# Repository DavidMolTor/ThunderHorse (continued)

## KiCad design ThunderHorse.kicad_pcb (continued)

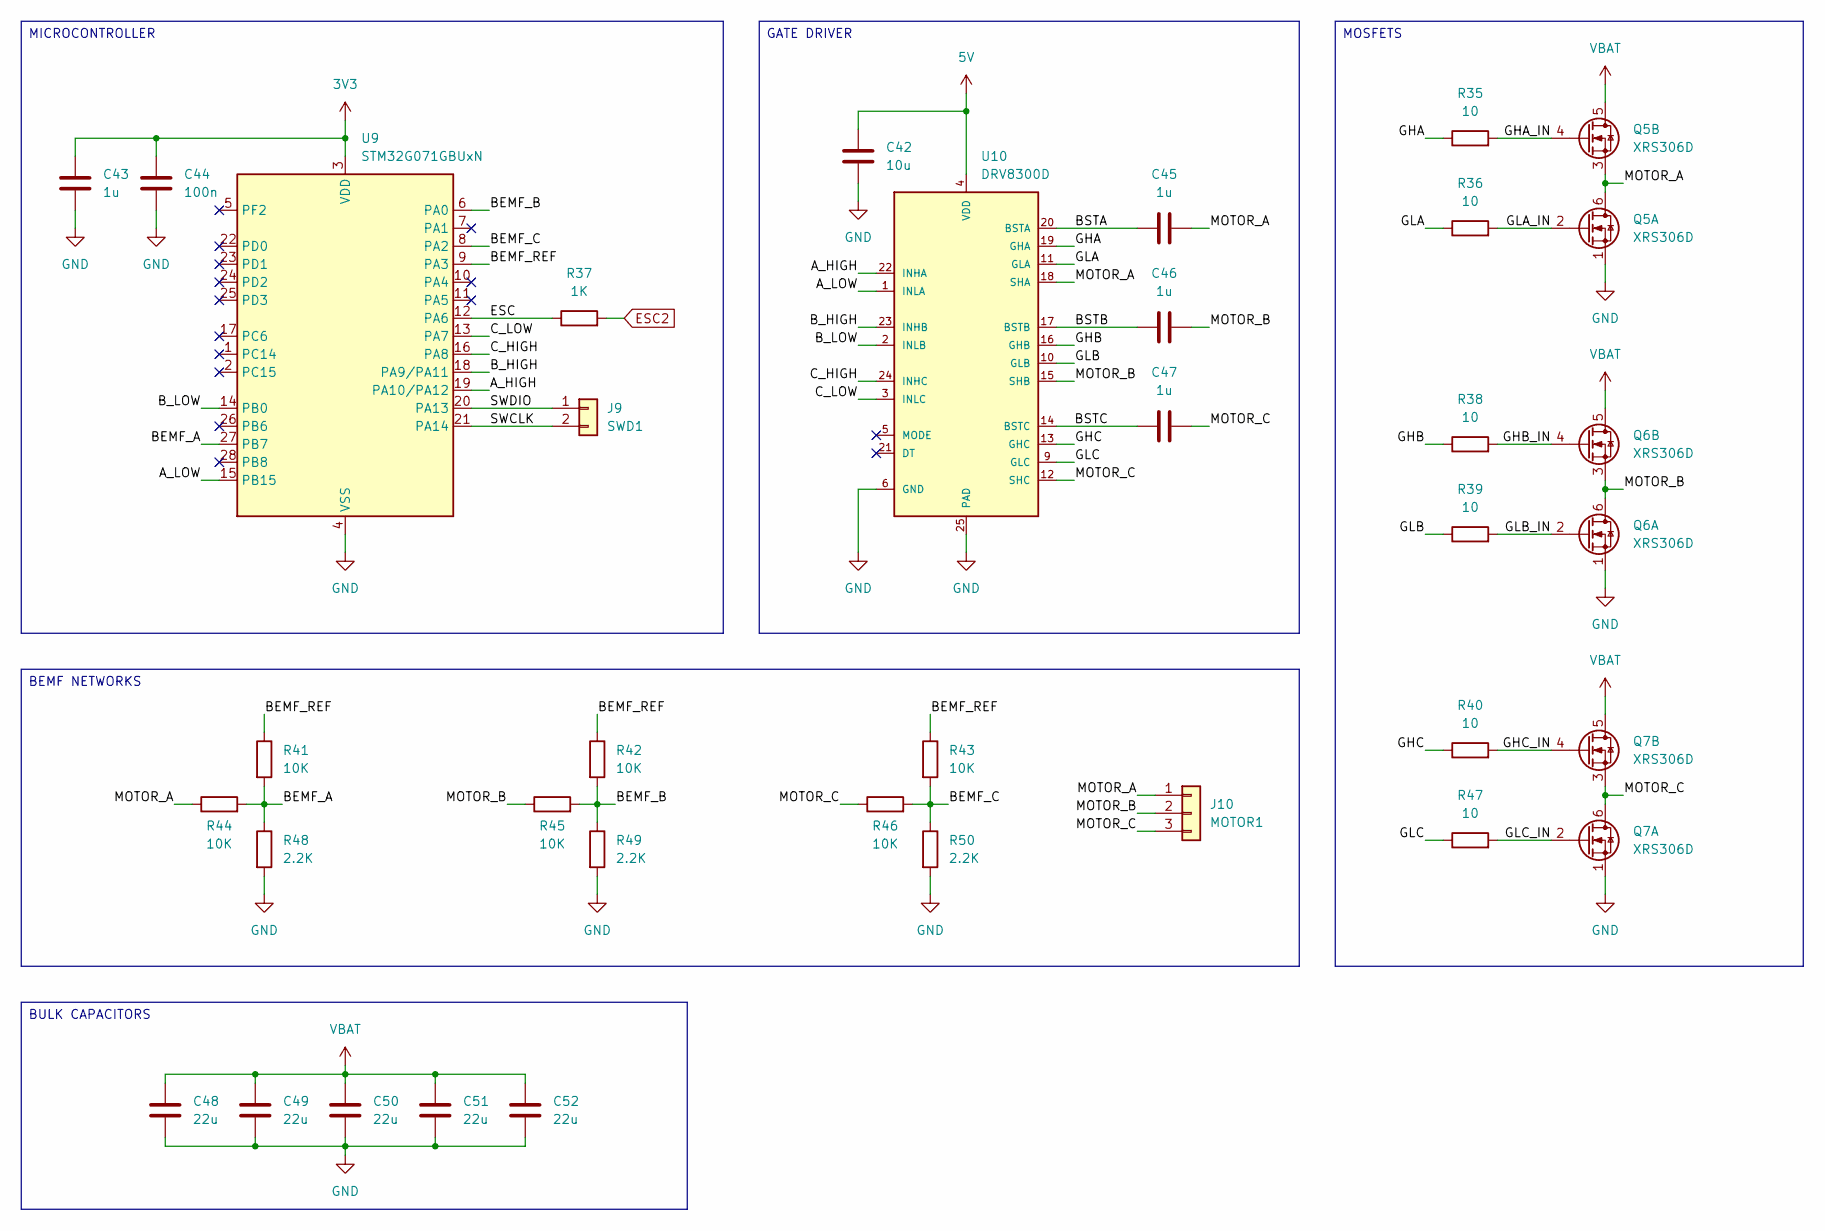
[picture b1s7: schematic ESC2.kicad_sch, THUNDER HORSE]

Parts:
C42: 10u; C_0603_1608Metric
C43, C45, C46, C47: 1u; C_0603_1608Metric
C44: 100n; C_0603_1608Metric
C48, C49, C50, C51, C52: 22u; C_1206_3216Metric
J9: SWD1; PAD_2_SQUARE_SOLID_1.0x1.0mm_P1.5mm
J10: MOTOR1; PAD_3_SQUARE_SOLID_2.5x2.5mm_P4.0mm_MOTOR
Q5, Q6, Q7: XRS306D; PDFN8_DUAL_3.3x3.3mm
R35, R36, R38, R39, R40, R47: 10; R_0603_1608Metric
R37: 1K; R_0603_1608Metric
R41, R42, R43, R44, R45, R46: 10K; R_0603_1608Metric
R48, R49, R50: 2.2K; R_0603_1608Metric
U9: STM32G071GBUxN; QFN-28_4x4mm_P0.5mm
U10: DRV8300D; VQFN-24-1EP_4x4mm_P0.5mm_EP2.45x2.45mm

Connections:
3V3: C43.1, C44.1, U9.3 (VDD); also elsewhere on the board
5V: C42.1, U10.4 (VDD); also elsewhere on the board
/ESC/ESC2/A_HIGH: U9.19 (PA10/PA12), U10.22 (INHA)
/ESC/ESC2/A_LOW: U9.15 (PB15), U10.1 (INLA)
/ESC/ESC2/BEMF_A: R41.2, R44.2, R48.1, U9.27 (PB7)
/ESC/ESC2/BEMF_B: R42.2, R45.2, R49.1, U9.6 (PA0)
/ESC/ESC2/BEMF_C: R43.2, R46.2, R50.1, U9.8 (PA2)
/ESC/ESC2/BEMF_REF: R41.1, R42.1, R43.1, U9.9 (PA3)
/ESC/ESC2/BSTA: C45.1, U10.20 (BSTA)
/ESC/ESC2/BSTB: C46.1, U10.17 (BSTB)
/ESC/ESC2/BSTC: C47.1, U10.14 (BSTC)
/ESC/ESC2/B_HIGH: U9.18 (PA9/PA11), U10.23 (INHB)
/ESC/ESC2/B_LOW: U9.14 (PB0), U10.2 (INLB)
/ESC/ESC2/C_HIGH: U9.16 (PA8), U10.24 (INHC)
/ESC/ESC2/C_LOW: U9.13 (PA7), U10.3 (INLC)
/ESC/ESC2/ESC: R37.1, U9.12 (PA6)
/ESC/ESC2/GHA: R35.1, U10.19 (GHA)
/ESC/ESC2/GHA_IN: Q5.4 (G), R35.2
/ESC/ESC2/GHB: R38.1, U10.16 (GHB)
/ESC/ESC2/GHB_IN: Q6.4 (G), R38.2
/ESC/ESC2/GHC: R40.1, U10.13 (GHC)
/ESC/ESC2/GHC_IN: Q7.4 (G), R40.2
/ESC/ESC2/GLA: R36.1, U10.11 (GLA)
/ESC/ESC2/GLA_IN: Q5.2 (G), R36.2
/ESC/ESC2/GLB: R39.1, U10.10 (GLB)
/ESC/ESC2/GLB_IN: Q6.2 (G), R39.2
/ESC/ESC2/GLC: R47.1, U10.9 (GLC)
/ESC/ESC2/GLC_IN: Q7.2 (G), R47.2
/ESC/ESC2/MOTOR_A: C45.2, J10.1, Q5.3 (S), Q5.6 (D), R44.1, U10.18 (SHA)
/ESC/ESC2/MOTOR_B: C46.2, J10.2, Q6.3 (S), Q6.6 (D), R45.1, U10.15 (SHB)
/ESC/ESC2/MOTOR_C: C47.2, J10.3, Q7.3 (S), Q7.6 (D), R46.1, U10.12 (SHC)
/ESC/ESC2/SWCLK: J9.2, U9.21 (PA14)
/ESC/ESC2/SWDIO: J9.1, U9.20 (PA13)
ESC2: R37.2; also elsewhere on the board
GND: C42.2, C43.2, C44.2, C48.2, C49.2, C50.2, C51.2, C52.2, Q5.1 (S), Q6.1 (S), Q7.1 (S), R48.2, R49.2, R50.2, U9.4 (VSS), U10.6 (GND), U10.25 (PAD); also elsewhere on the board
VBAT: C48.1, C49.1, C50.1, C51.1, C52.1, Q5.5 (D), Q6.5 (D), Q7.5 (D); also elsewhere on the board

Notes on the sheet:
MICROCONTROLLER
BULK CAPACITORS
BEMF NETWORKS
MOSFETS
GATE DRIVER

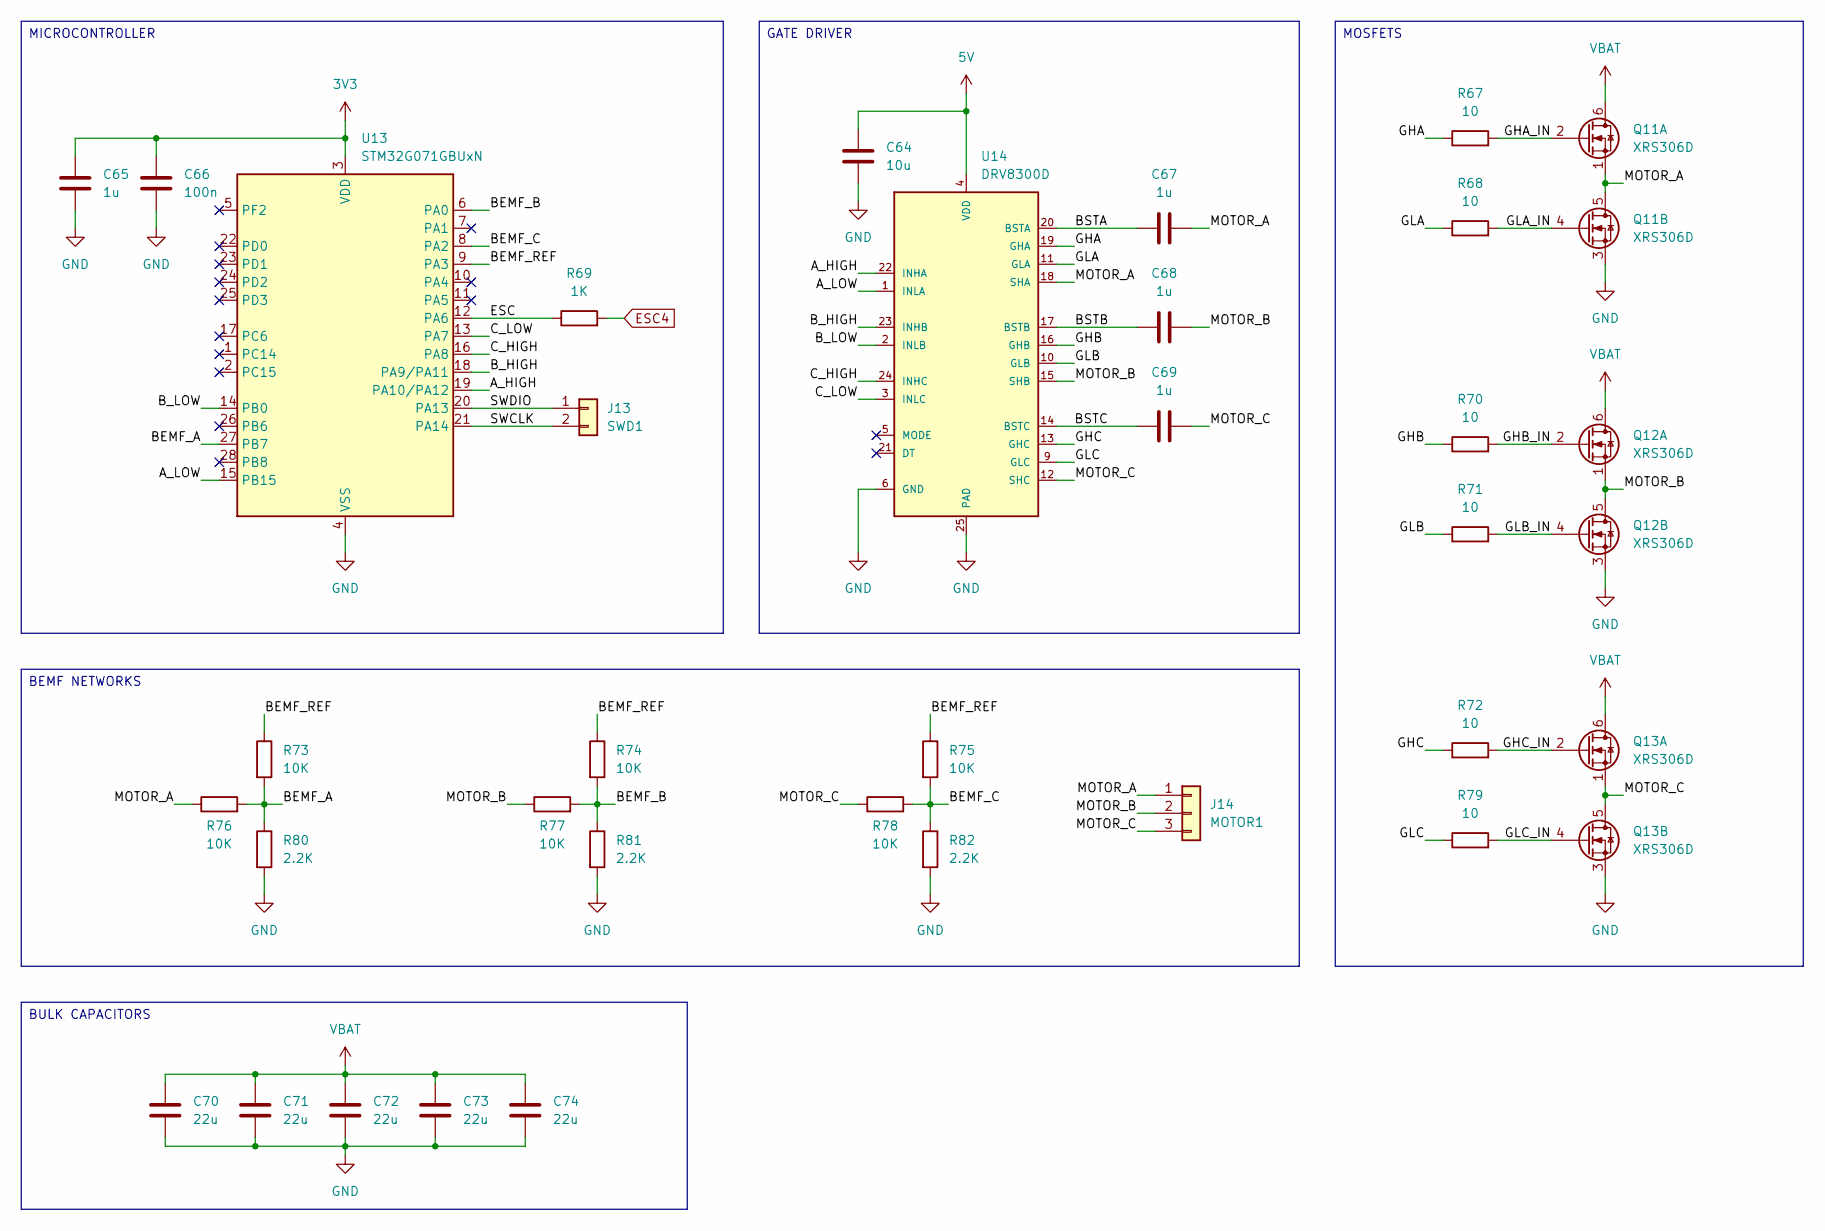
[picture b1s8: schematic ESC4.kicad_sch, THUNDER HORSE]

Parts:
C64: 10u; C_0603_1608Metric
C65, C67, C68, C69: 1u; C_0603_1608Metric
C66: 100n; C_0603_1608Metric
C70, C71, C72, C73, C74: 22u; C_1206_3216Metric
J13: SWD1; PAD_2_SQUARE_SOLID_1.0x1.0mm_P1.5mm
J14: MOTOR1; PAD_3_SQUARE_SOLID_2.5x2.5mm_P4.0mm_MOTOR
Q11, Q12, Q13: XRS306D; PDFN8_DUAL_3.3x3.3mm
R67, R68, R70, R71, R72, R79: 10; R_0603_1608Metric
R69: 1K; R_0603_1608Metric
R73, R74, R75, R76, R77, R78: 10K; R_0603_1608Metric
R80, R81, R82: 2.2K; R_0603_1608Metric
U13: STM32G071GBUxN; QFN-28_4x4mm_P0.5mm
U14: DRV8300D; VQFN-24-1EP_4x4mm_P0.5mm_EP2.45x2.45mm

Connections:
3V3: C65.1, C66.1, U13.3 (VDD); also elsewhere on the board
5V: C64.1, U14.4 (VDD); also elsewhere on the board
/ESC/ESC4/A_HIGH: U13.19 (PA10/PA12), U14.22 (INHA)
/ESC/ESC4/A_LOW: U13.15 (PB15), U14.1 (INLA)
/ESC/ESC4/BEMF_A: R73.2, R76.2, R80.1, U13.27 (PB7)
/ESC/ESC4/BEMF_B: R74.2, R77.2, R81.1, U13.6 (PA0)
/ESC/ESC4/BEMF_C: R75.2, R78.2, R82.1, U13.8 (PA2)
/ESC/ESC4/BEMF_REF: R73.1, R74.1, R75.1, U13.9 (PA3)
/ESC/ESC4/BSTA: C67.1, U14.20 (BSTA)
/ESC/ESC4/BSTB: C68.1, U14.17 (BSTB)
/ESC/ESC4/BSTC: C69.1, U14.14 (BSTC)
/ESC/ESC4/B_HIGH: U13.18 (PA9/PA11), U14.23 (INHB)
/ESC/ESC4/B_LOW: U13.14 (PB0), U14.2 (INLB)
/ESC/ESC4/C_HIGH: U13.16 (PA8), U14.24 (INHC)
/ESC/ESC4/C_LOW: U13.13 (PA7), U14.3 (INLC)
/ESC/ESC4/ESC: R69.1, U13.12 (PA6)
/ESC/ESC4/GHA: R67.1, U14.19 (GHA)
/ESC/ESC4/GHA_IN: Q11.2 (G), R67.2
/ESC/ESC4/GHB: R70.1, U14.16 (GHB)
/ESC/ESC4/GHB_IN: Q12.2 (G), R70.2
/ESC/ESC4/GHC: R72.1, U14.13 (GHC)
/ESC/ESC4/GHC_IN: Q13.2 (G), R72.2
/ESC/ESC4/GLA: R68.1, U14.11 (GLA)
/ESC/ESC4/GLA_IN: Q11.4 (G), R68.2
/ESC/ESC4/GLB: R71.1, U14.10 (GLB)
/ESC/ESC4/GLB_IN: Q12.4 (G), R71.2
/ESC/ESC4/GLC: R79.1, U14.9 (GLC)
/ESC/ESC4/GLC_IN: Q13.4 (G), R79.2
/ESC/ESC4/MOTOR_A: C67.2, J14.1, Q11.1 (S), Q11.5 (D), R76.1, U14.18 (SHA)
/ESC/ESC4/MOTOR_B: C68.2, J14.2, Q12.1 (S), Q12.5 (D), R77.1, U14.15 (SHB)
/ESC/ESC4/MOTOR_C: C69.2, J14.3, Q13.1 (S), Q13.5 (D), R78.1, U14.12 (SHC)
/ESC/ESC4/SWCLK: J13.2, U13.21 (PA14)
/ESC/ESC4/SWDIO: J13.1, U13.20 (PA13)
ESC4: R69.2; also elsewhere on the board
GND: C64.2, C65.2, C66.2, C70.2, C71.2, C72.2, C73.2, C74.2, Q11.3 (S), Q12.3 (S), Q13.3 (S), R80.2, R81.2, R82.2, U13.4 (VSS), U14.6 (GND), U14.25 (PAD); also elsewhere on the board
VBAT: C70.1, C71.1, C72.1, C73.1, C74.1, Q11.6 (D), Q12.6 (D), Q13.6 (D); also elsewhere on the board

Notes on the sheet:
GATE DRIVER
MICROCONTROLLER
MOSFETS
BULK CAPACITORS
BEMF NETWORKS

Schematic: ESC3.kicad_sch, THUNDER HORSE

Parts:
C53: 10u; C_0603_1608Metric
C54, C56, C57, C58: 1u; C_0603_1608Metric
C55: 100n; C_0603_1608Metric
C59, C60, C61, C62, C63: 22u; C_1206_3216Metric
J11: SWD1; PAD_2_SQUARE_SOLID_1.0x1.0mm_P1.5mm
J12: MOTOR1; PAD_3_SQUARE_SOLID_2.5x2.5mm_P4.0mm_MOTOR
Q8, Q9, Q10: XRS306D; PDFN8_DUAL_3.3x3.3mm
R51, R52, R54, R55, R56, R63: 10; R_0603_1608Metric
R53: 1K; R_0603_1608Metric
R57, R58, R59, R60, R61, R62: 10K; R_0603_1608Metric
R64, R65, R66: 2.2K; R_0603_1608Metric
U11: STM32G071GBUxN; QFN-28_4x4mm_P0.5mm
U12: DRV8300D; VQFN-24-1EP_4x4mm_P0.5mm_EP2.45x2.45mm

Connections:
3V3: C54.1, C55.1, U11.3 (VDD); also elsewhere on the board
5V: C53.1, U12.4 (VDD); also elsewhere on the board
/ESC/ESC3/A_HIGH: U11.19 (PA10/PA12), U12.22 (INHA)
/ESC/ESC3/A_LOW: U11.15 (PB15), U12.1 (INLA)
/ESC/ESC3/BEMF_A: R57.2, R60.2, R64.1, U11.27 (PB7)
/ESC/ESC3/BEMF_B: R58.2, R61.2, R65.1, U11.6 (PA0)
/ESC/ESC3/BEMF_C: R59.2, R62.2, R66.1, U11.8 (PA2)
/ESC/ESC3/BEMF_REF: R57.1, R58.1, R59.1, U11.9 (PA3)
/ESC/ESC3/BSTA: C56.1, U12.20 (BSTA)
/ESC/ESC3/BSTB: C57.1, U12.17 (BSTB)
/ESC/ESC3/BSTC: C58.1, U12.14 (BSTC)
/ESC/ESC3/B_HIGH: U11.18 (PA9/PA11), U12.23 (INHB)
/ESC/ESC3/B_LOW: U11.14 (PB0), U12.2 (INLB)
/ESC/ESC3/C_HIGH: U11.16 (PA8), U12.24 (INHC)
/ESC/ESC3/C_LOW: U11.13 (PA7), U12.3 (INLC)
/ESC/ESC3/ESC: R53.1, U11.12 (PA6)
/ESC/ESC3/GHA: R51.1, U12.19 (GHA)
/ESC/ESC3/GHA_IN: Q8.4 (G), R51.2
/ESC/ESC3/GHB: R54.1, U12.16 (GHB)
/ESC/ESC3/GHB_IN: Q9.4 (G), R54.2
/ESC/ESC3/GHC: R56.1, U12.13 (GHC)
/ESC/ESC3/GHC_IN: Q10.4 (G), R56.2
/ESC/ESC3/GLA: R52.1, U12.11 (GLA)
/ESC/ESC3/GLA_IN: Q8.2 (G), R52.2
/ESC/ESC3/GLB: R55.1, U12.10 (GLB)
/ESC/ESC3/GLB_IN: Q9.2 (G), R55.2
/ESC/ESC3/GLC: R63.1, U12.9 (GLC)
/ESC/ESC3/GLC_IN: Q10.2 (G), R63.2
/ESC/ESC3/MOTOR_A: C56.2, J12.1, Q8.3 (S), Q8.6 (D), R60.1, U12.18 (SHA)
/ESC/ESC3/MOTOR_B: C57.2, J12.2, Q9.3 (S), Q9.6 (D), R61.1, U12.15 (SHB)
/ESC/ESC3/MOTOR_C: C58.2, J12.3, Q10.3 (S), Q10.6 (D), R62.1, U12.12 (SHC)
/ESC/ESC3/SWCLK: J11.2, U11.21 (PA14)
/ESC/ESC3/SWDIO: J11.1, U11.20 (PA13)
ESC3: R53.2; also elsewhere on the board
GND: C53.2, C54.2, C55.2, C59.2, C60.2, C61.2, C62.2, C63.2, Q8.1 (S), Q9.1 (S), Q10.1 (S), R64.2, R65.2, R66.2, U11.4 (VSS), U12.6 (GND), U12.25 (PAD); also elsewhere on the board
VBAT: C59.1, C60.1, C61.1, C62.1, C63.1, Q8.5 (D), Q9.5 (D), Q10.5 (D); also elsewhere on the board

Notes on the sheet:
MOSFETS
GATE DRIVER
BULK CAPACITORS
BEMF NETWORKS
MICROCONTROLLER

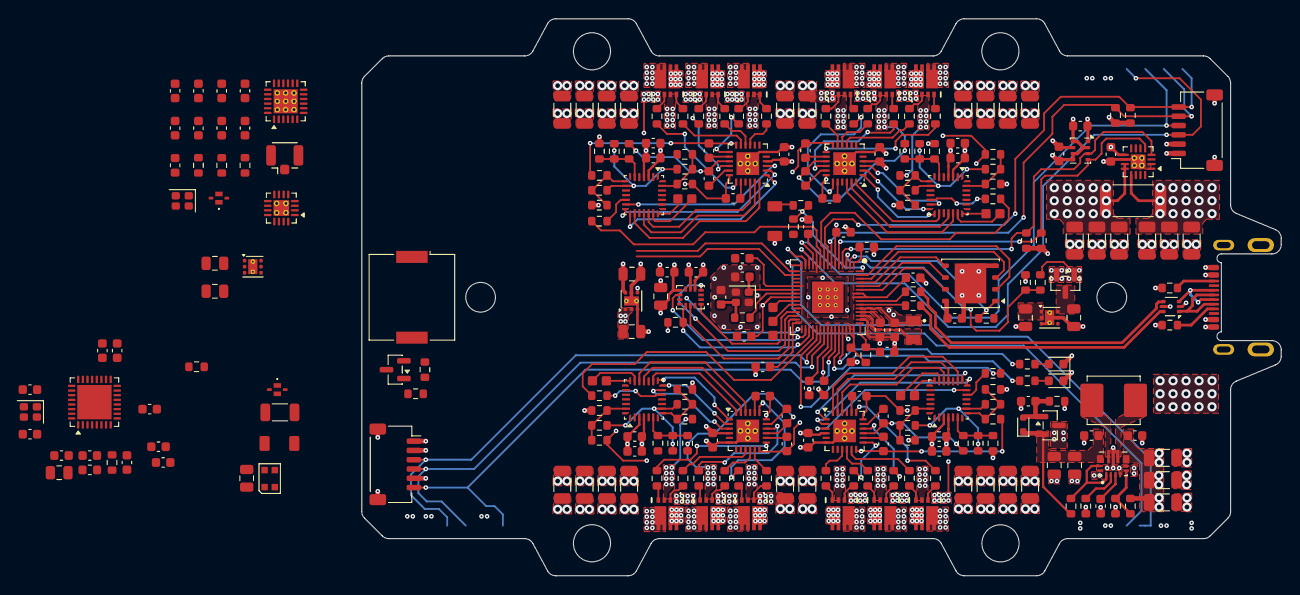
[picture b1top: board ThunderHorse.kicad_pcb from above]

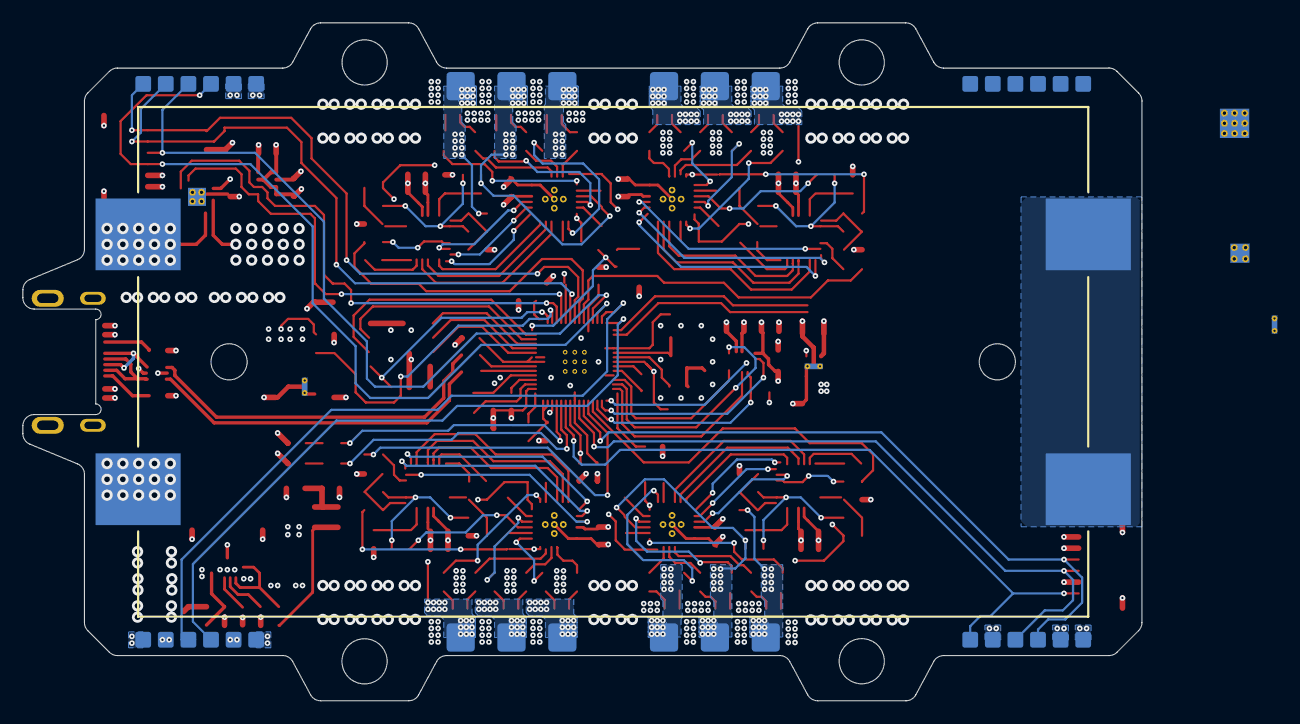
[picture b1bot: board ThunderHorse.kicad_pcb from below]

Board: 6 copper layers, 99.1 x 60.0 mm, 277 parts (13 on the bottom side), 225 nets.

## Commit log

2026-01-28 Initial commit
    Added the readme file.
    Added the ignore file.
    Added the initial project files.
2026-01-28 Removed attributes
    Removed the attributes file.
2026-01-29 Schematic structure
    Added new schematic sheets.
    Updated the main project.
2026-02-01 Receiver design
    Updated the receiver design for the SX1280.
    Added an ignore for lock files.
    Minor schematic updates.
2026-02-01 Receiver design
    Updated the receiver schematic.
    TODO:
    Review the receiver schematic.
    Implement sensor conditioning.
2026-02-02 Sensors design
    Updated the inertial measurement unit schematic.
    Updated the power monitor schematic.
    Updated the barometer schematic.
    Updated the receiver schematic.
    TODO:
    Review the sensors schematic.
2026-02-03 ESC design
    Updated the ESC schematic.
    Replaces the INA 226 with INA230.
2026-02-05 MCU design
    Updated the main RP2350 schematic.
    Updated labels for other designs.
2026-02-05 Complete ESC and MCU
    Added the 4 ESC to the eschematic.
    Updated the MCU design to add the connectors and buzzer.
2026-02-05 Power design
    Added the 5V regulator schematic.
    Updated the MCU schematic.
    Updated the RX schematic.
    Updated the sensors schematic.
    TODO:
    Calculate the voltage divider for the 5V regulator.
2026-02-06 Footprints and revision
    Added the missing footprints.
    Updated a all the schematics.
    Completed an initial review of the schematics.
    TODO:
    Perform a deep review of the schematics before committing to layout.
2026-02-07 New sheet
    Added a sheet for extra modules.
2026-02-07 ESC design
    Updated the ESC schematics.
2026-02-07 Receiver and sensors
    Updated the receiver schematic.
    Updated the sensors schematic.
    Removed the ESP32 C3.
2026-02-07 Power and MCU
    Updated the power schematic.
    Updated the MCU schematic.
    TODO:
    Merge with features branch.
    Review all schematics prior to layout.
2026-02-07 MCU design
    Updated the MCU schematic.
    TODO:
    Add a bind button connected to the MCU.
2026-02-08 Connectors and tag
    Added bulk capacitance for each ESC.
    Added SWD connector.
    Updated all tags.
    TODO:
    Add pads for the unconnected GPIO pins.
2026-02-08 Missing labels and revision
    First complete revision of the schematic.
    Added missing labels.
    TODO:
    Continue reviewing the schematic.
    Include net coloring.
2026-02-08 Initial layout
    Added the components to the board.
    TODO:
    Review the schematic before continuing the layout.
2026-02-08 Net nodes
    Added the missing net nodes in the schematic.
2026-02-09 Net nodes and layout
    Updated all net nodes definitions.
    Updated the board layout.
    TODO:
    Define the net dimensions for the layout.
2026-02-09 Board outline and net nodes
    Added an initial board outline.
    Updated net nodes definitions.
    Updated board rules for manufacturing.
2026-02-10 ESC layout and footprints
    Added the initial ESC layout.
    Updated some footprints for compatibility.
2026-02-12 Layout replication
    Updated the ESC schematic to allow for layout replication.
    Updated the PCB layout.
2026-02-14 Initial layout
    Completed an initial layout of the main components.
    TODO
    Route the ESCs and check the result.
2026-02-15 Settings and ESC layout
    Updated the PCB configuration options for manufacturing.
    Completed the initial ESC layout.
    TODO:
    Replicate ESC layout.
2026-02-16 License and ESC layout
    Added a file extension to the license.
    Updated the second ESC layout.
    TODO:
    Continue the ESC layout.
2026-02-17 ESC layout
    Updated the layout for the final ESC.
2026-02-17 MCU layout
    Started the MCU layout.
    TODO:
    Check the previous iterations.
2026-02-18 IMU layout
    Completed the IMU layout.
    TODO:
    Continue with the transceiver routing.
    Connect each ESC to the MCU.
2026-02-20 MCU layout
    Updated the schematic labels.
    Continued the MCU layout.
2026-02-22 Schematic revision
    Added an ESP32 C3 for the ELRS receiver.
    Updated the protection approach for the board.
    Updated the net nodes.
2026-02-24 Schematic and PCB
    Reviewed the schematic and deleted unused components.
    Updated the PCB and also removed unused footprints.
2026-02-25 IMU filtering and layout
    Added a missing capacitor for the IMU.
    Updated the PCB layout.
2026-02-27 Oscillator and IMU layout
    Updated the oscillator layout for the RP2350.
    Updated the IMU layout for the IMU.
2026-03-01 Power and ESC layout
    Updated the power layout.
    Updated the ESC layout.
    TODO:
    Improve track spacing for the ESC.
    Complete the power connections.
2026-03-05 ESC layout and connections
    Updated an alignment issue with some ESC layouts.
    Added power connections.
2026-03-06 Power layout and regulators
    Changed the LDO regulators to TLV767.
    Added missing power connections.
    TODO:
    Start the ELRS module layout.
    Review previous iterations.
2026-03-21 Voltage detection
    Added a VBUS voltage detection for the RP.
    Minor layout changes.
